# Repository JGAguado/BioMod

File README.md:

[![GitHub Release][releases-shield]][releases]
[![License][license-shield]](LICENSE)

[![Project Maintenance][maintenance-shield]][maintenance]
[![BuyMeCoffee][buymecoffee-shield]][buymecoffee]

# BioMod
Mod for ArduLab, directly plugable via the Mod Interface. The BioMod is designed to allow ArduLab read diferent biological parameters and environmental conditions.

## Project tree

<li><a href="./Design/">Design</a></li>
<li><a href="./Documentation/">Documentation</a></li>

<li><a href="./README.md">README.md</a></li>

[releases-shield]: https://img.shields.io/github/release/JGAguado/BioMod.svg?style=for-the-badge
[releases]: https://github.com/JGAguado/BioMod/releases

[license-shield]: https://img.shields.io/badge/License-CC%20BY--NC--SA%204.0-lightgrey.svg?style=for-the-badge

[maintenance-shield]: https://img.shields.io/badge/maintainer-J.%20G.%20Aguado-blue.svg?style=for-the-badge
[maintenance]: https://github.com/JGAguado

[buymecoffee-shield]: https://img.shields.io/badge/buy%20me%20a%20coffee-support-yellow.svg?style=for-the-badge
[buymecoffee]: https://www.buymeacoffee.com/J.G.Aguado

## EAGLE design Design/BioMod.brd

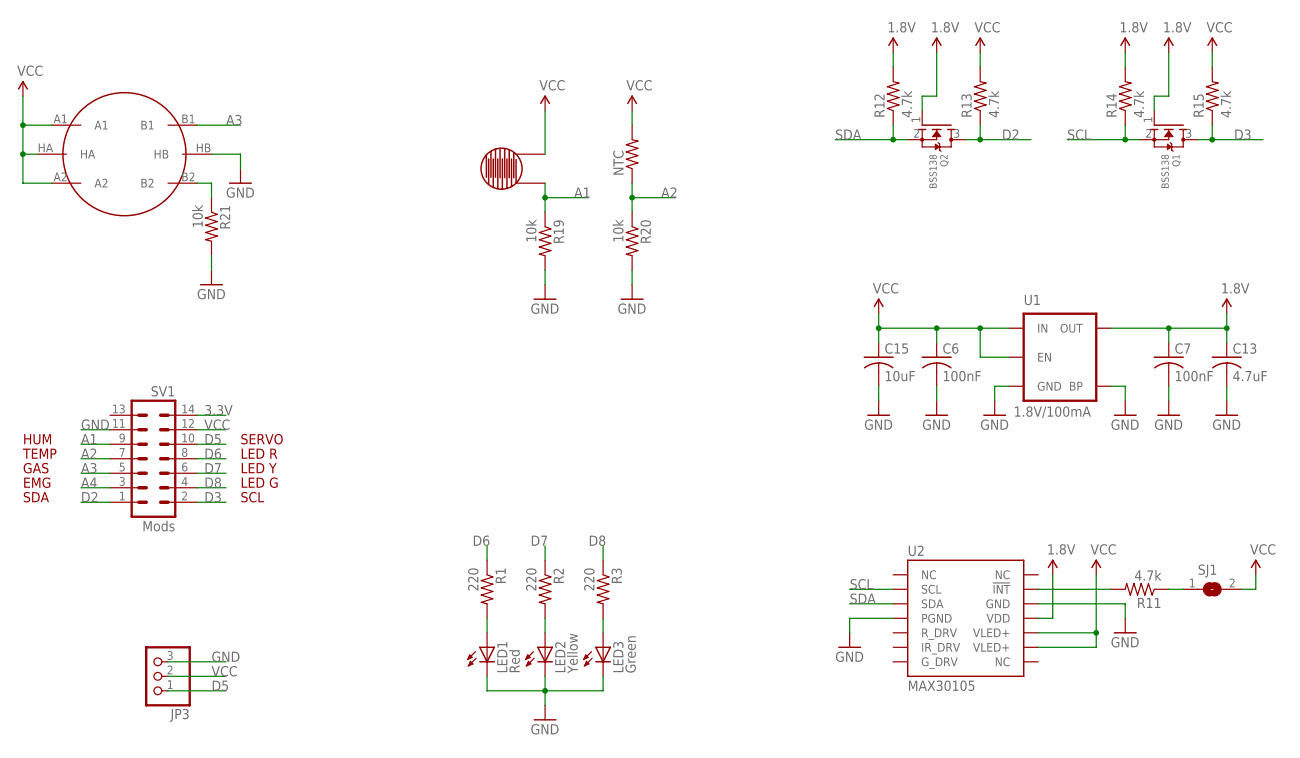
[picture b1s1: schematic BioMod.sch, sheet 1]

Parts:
C6, C7: 100nF; C1206
C13: 4.7uF; C1206
C15: 10uF; C1206
JP3: PINHD-1X3; 1X03
LED1: Red; 1206
LED2: Yellow; 1206
LED3: Green; 1206
NTC: R-US_R1206; R1206
Q1, Q2: BSS138; SOT23
R1, R2, R3: 220; R1206
R11, R12, R13, R14, R15: 4.7k; R1206
R19, R20, R21: 10k; R1206
SJ1: SJ
SNG: METHANE_SENSOR; MQ-3
SV1: Mods; MA07-2
U1: 1.8V/100mA; SC70
U2: MAX30105; OLGA-14
U$16: RESISTIVE_SENSOR_PAD

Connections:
1.8V: C7.1, C13.1, Q1.1 (G), Q2.1 (G), R12.2, R14.2, U1.5 (OUT), U2.11 (VDD)
3.3V: SV1.14
A1: R19.1, SV1.9, U$16.1
A2: NTC.1, R20.1, SV1.7
A3: SNG.B1, SV1.5
A4: SV1.3; also elsewhere on the board
D2: Q2.3 (D), R13.1, SV1.1
D3: Q1.3 (D), R15.1, SV1.2
D5: JP3.1, SV1.10
D6: R1.1, SV1.8
D7: R2.1, SV1.6
D8: R3.1, SV1.4
GND: C6.2, C7.2, C13.2, C15.2, JP3.3, LED1.C, LED2.C, LED3.C, R19.2, R20.2, R21.2, SNG.HB, SV1.11, U1.2 (GND), U1.4 (BP), U2.4 (PGND), U2.12 (GND); also elsewhere on the board
unnamed: R11.1, SJ1.1
unnamed: R11.2, U2.13 (!INT)
unnamed: R21.1, SNG.B2
unnamed: LED2.A, R2.2
unnamed: LED3.A, R3.2
unnamed: LED1.A, R1.2
SCL: Q1.2 (S), R14.1, U2.2 (SCL)
SDA: Q2.2 (S), R12.1, U2.3 (SDA)
VCC: C6.1, C15.1, JP3.2, NTC.2, R13.2, R15.2, SJ1.2, SNG.A1, SNG.A2, SNG.HA, SV1.12, U1.1 (IN), U1.3 (EN), U2.9 (VLED+), U2.10 (VLED+), U$16.0; also elsewhere on the board

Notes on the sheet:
SCL
SDA
HUM
TEMP
EMG
GAS
LED G
LED Y
LED R
SERVO

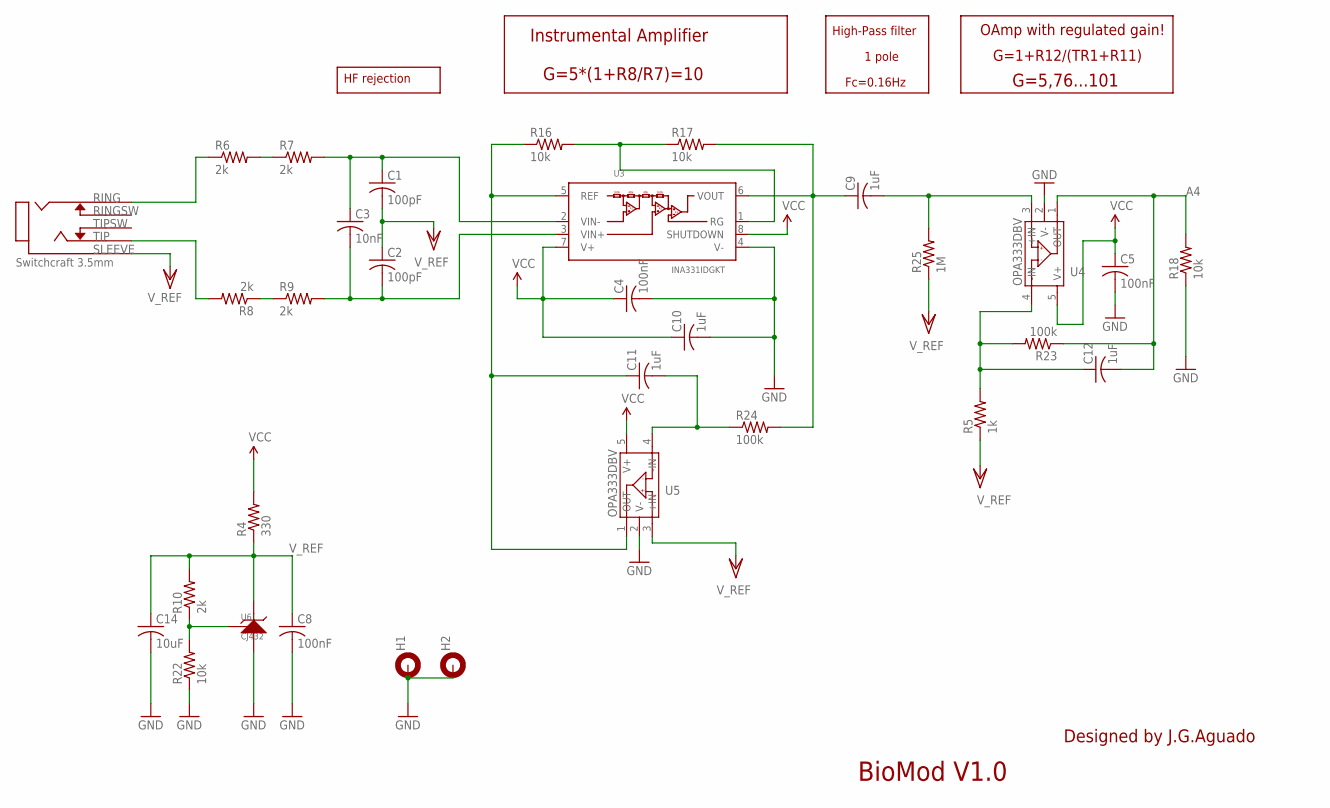
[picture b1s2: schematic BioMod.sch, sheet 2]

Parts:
C1, C2: 100pF; C1206
C3: 10nF; C1206
C4, C5, C8: 100nF; C1206
C9, C10, C11, C12: 1uF; C1206
C14: 10uF; C1206
H1, H2: MOUNT-PAD-ROUND3.2; 3,2-PAD
JC1: SWTCHCRFT_3.5JACK5-JACK-SMD; 4-JACK-SMD
R4: 330; R1206
R5: 1k; R1206
R6, R7, R8, R9, R10: 2k; R1206
R16, R17, R18, R22: 10k; R1206
R23, R24: 100k; R1206
R25: 1M; R1206
U3: INA331IDGKT; MSOP-8
U4, U5: OPA333DBV; SOT23-5
U6: CJ432; SOT23

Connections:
A4: C12.2, R18.2, R23.1, U4.1 (OUT); also elsewhere on the board
GND: C4.2, C5.2, C8.2, C10.2, C14.2, H1.B3,2, H2.B3,2, R18.1, R22.1, U3.4 (V-), U4.2 (V-), U5.2 (V-), U6.3 (A); also elsewhere on the board
unnamed: R8.1, R9.1
unnamed: C11.2, R24.1, U5.4 (-IN)
unnamed: R6.2, R7.1
unnamed: C11.1, R16.1, U3.5 (REF), U5.1 (OUT)
unnamed: R16.2, R17.1, U3.1 (RG)
unnamed: JC1.2, R6.1
unnamed: JC1.3, R8.2
unnamed: R10.1, R22.2, U6.1 (R)
unnamed: C9.1, R17.2, R24.2, U3.6 (VOUT)
unnamed: C2.2, C3.2, R9.2, U3.3 (VIN+)
unnamed: C1.1, C3.1, R7.2, U3.2 (VIN-)
unnamed: C9.2, R25.2, U4.3 (+IN)
unnamed: C12.1, R5.2, R23.2, U4.4 (-IN)
VCC: C4.1, C5.1, C10.1, R4.2, U3.7 (V+), U3.8 (SHUTDOWN), U4.5 (V+), U5.5 (V+); also elsewhere on the board
V_REF: C1.2, C2.1, C8.1, C14.1, JC1.1, R4.1, R5.1, R10.2, R25.1, U5.3 (+IN), U6.2 (K)

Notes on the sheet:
BioMod V1.0
Designed by J.G.Aguado
G=1+R12/(TR1+R11)
G=5,76...101
Fc=0.16Hz
HF rejection
High-Pass filter
OAmp with regulated gain!
1 pole
G=5*(1+R8/R7)=10
Instrumental Amplifier

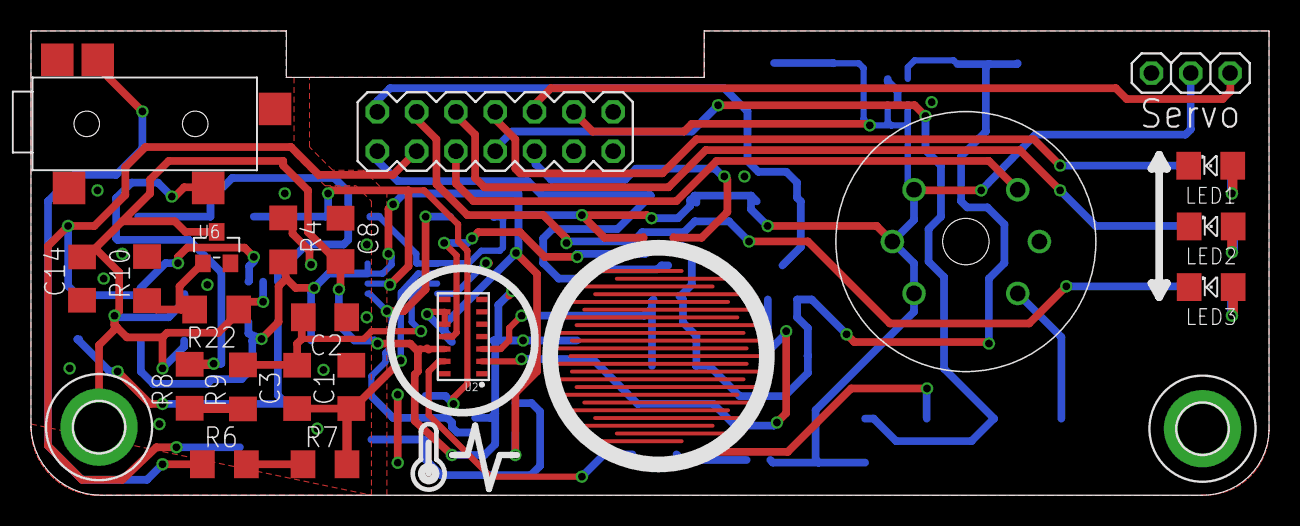
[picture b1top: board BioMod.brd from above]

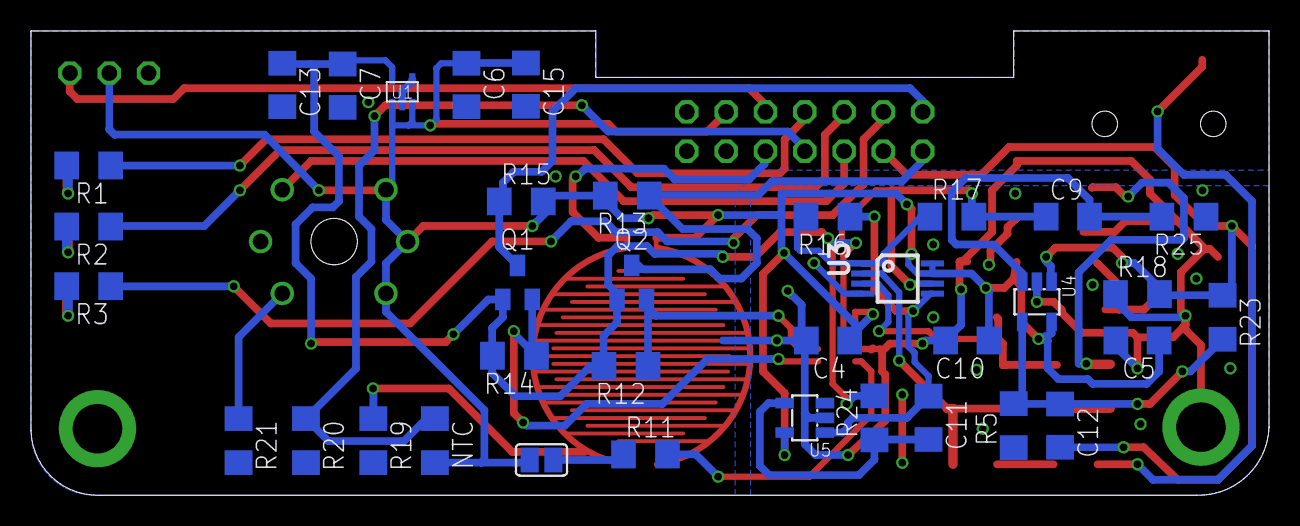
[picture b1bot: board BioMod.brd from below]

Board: 2 copper layers, 80.0 x 30.0 mm, 60 parts (36 on the bottom side), 35 nets.

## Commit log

2022-04-15 Updated structure

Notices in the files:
parts and their libraries:
SparkFun-PowerIC: Licensing: Creative Commons ShareAlike 4.0 International - https://creativecommons.org/licenses/by-sa/4.0
SparkFun-Aesthetics: Licensing: CC v3.0 Share-Alike You are welcome to use this library for commercial purposes.
